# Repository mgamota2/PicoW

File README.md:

# picoW
Raspberry Pi Pico W Projects

## Overview
All of these projects are personal projects which I have completed and implemented. Justifications and media can be found on my github.io page. I have found the Pico W to be an extremely versatile platform for the development of all kinds of embedded systems projects. All of these projects use the on-board WiFi chip.

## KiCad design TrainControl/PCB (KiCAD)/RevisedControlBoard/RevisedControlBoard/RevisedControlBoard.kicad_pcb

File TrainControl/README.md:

# DC Train Control
This project offers an LAN solution for DC model train control

## Overview
This project includes both hardware design and firmware for the Raspberry Pi Pico written in Micropython. The hardware is designed as a hub which can control the speed and
direction of the train as well as switch electrically switching tracks. The hub is controlled from a Raspberry Pi Pico hosted web server which has a dashboard for user 
inputs, allowing remote control of the train

## File Descriptions
**Files in the Full Control folder support track switching, speed, and direction while files in the Speed Control folder only support speed control.

index.html : This file contains the HTML, CSS, and JavaScript code to create, style, and add functionality to the slider and buttons.

main.py : This file initilizes a train object and parses requests from the server to evaluate user input and change speedm direction, or switching tracks accordingly

train_func.py : This file defines the trackPins and railPins classes which correspond to the switching tracks and train direction and speed, respectively

wifi_init.py : This file defines a helper function to connect the Pico W to a WiFi network and establish the server

### PCB
Since this project includes hardware design, the KiCAD project files are provided. Files under RevisedControlBoard are the working version

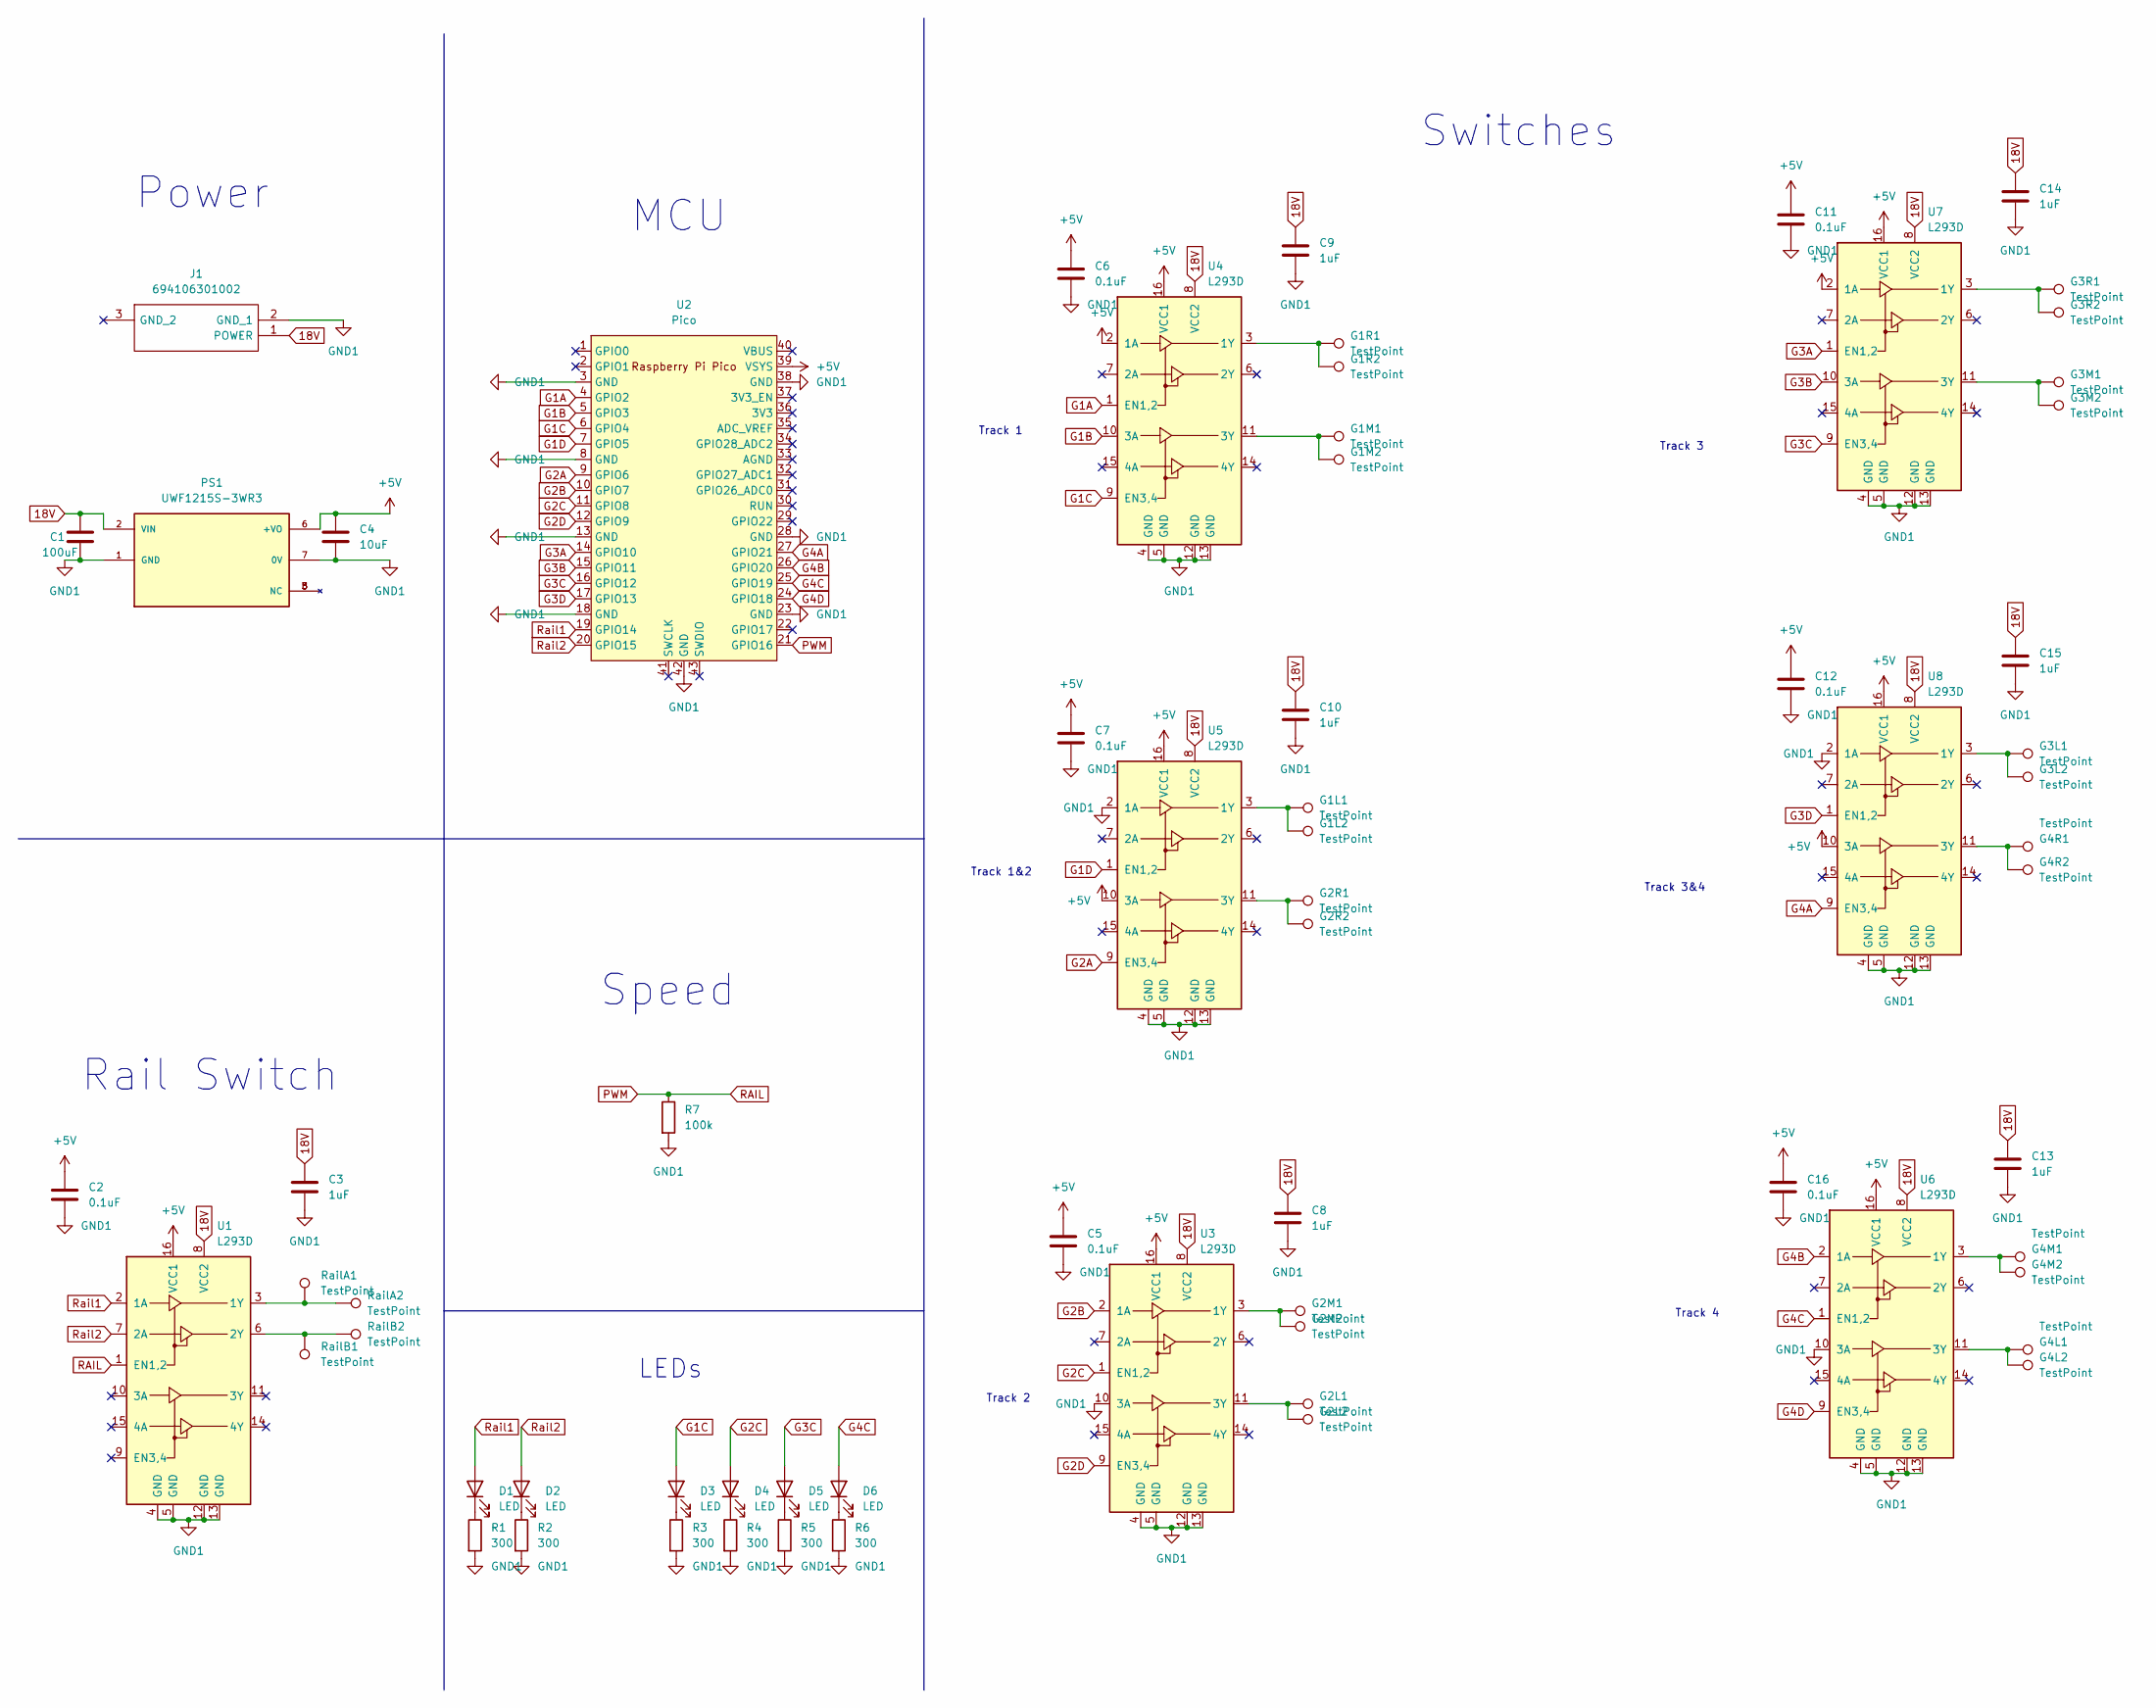
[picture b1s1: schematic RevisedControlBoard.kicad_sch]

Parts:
C1: 100uF; C_1210_3225Metric
C2, C5, C6, C7, C11, C12, C16: 0.1uF; C_1210_3225Metric
C3, C8, C9, C10, C13, C14, C15: 1uF; C_1210_3225Metric
C4: 10uF; C_1210_3225Metric
D1, D2, D3, D4, D5, D6: LED; LED_1812_4532Metric
G1L1, G1L2, G1M1, G1M2, G1R1, G1R2, G2L1, G2L2, G2M1, G2M2, G2R1, G2R2, G3L1, G3L2, G3M1, G3M2, G3R1, G3R2, G4L1, G4L2, G4M1, G4M2, G4R1, G4R2: TestPoint; TestPoint_Pad_2.5x2.5mm
J1: 694106301002; 694106301002_1; Mouser Part Number 710-694106301002
PS1: UWF1215S-3WR3; CONV_UWF1215S-3WR3; PARTREV 2020.08.11-A/1
R1, R2, R3, R4, R5, R6: 300; R_1210_3225Metric
R7: 100k; R_1210_3225Metric
RailA1, RailA2: TestPoint; TestPoint_Pad_2.5x2.5mm
RailB1, RailB2: TestPoint; TestPoint_Pad_2.5x2.5mm
U1, U3, U4, U5, U6, U7, U8: L293D; DIP-16_W7.62mm
U2: Pico; RPi_Pico_SMD_TH

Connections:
18V: C1.1, C3.1, C8.1, C9.1, C10.1, C13.1, C14.1, C15.1, J1.1 (POWER), PS1.2 (VIN), U1.8 (VCC2), U3.8 (VCC2), U4.8 (VCC2), U5.8 (VCC2), U6.8 (VCC2), U7.8 (VCC2), U8.8 (VCC2)
+5V: C2.1, C4.1, C5.1, C6.1, C7.1, C11.1, C12.1, C16.1, PS1.6 (+VO), U1.16 (VCC1), U2.39 (VSYS), U3.16 (VCC1), U4.2 (1A), U4.16 (VCC1), U5.10 (3A), U5.16 (VCC1), U6.16 (VCC1), U7.2 (1A), U7.16 (VCC1), U8.10 (3A), U8.16 (VCC1)
G1A: U2.4 (GPIO2), U4.1 (EN1,2)
G1B: U2.5 (GPIO3), U4.10 (3A)
G1C: D3.2 (A), U2.6 (GPIO4), U4.9 (EN3,4)
G1D: U2.7 (GPIO5), U5.1 (EN1,2)
G2A: U2.9 (GPIO6), U5.9 (EN3,4)
G2B: U2.10 (GPIO7), U3.2 (1A)
G2C: D4.2 (A), U2.11 (GPIO8), U3.1 (EN1,2)
G2D: U2.12 (GPIO9), U3.9 (EN3,4)
G3A: U2.14 (GPIO10), U7.1 (EN1,2)
G3B: U2.15 (GPIO11), U7.10 (3A)
G3C: D5.2 (A), U2.16 (GPIO12), U7.9 (EN3,4)
G3D: U2.17 (GPIO13), U8.1 (EN1,2)
G4A: U2.27 (GPIO21), U8.9 (EN3,4)
G4B: U2.26 (GPIO20), U6.2 (1A)
G4C: D6.2 (A), U2.25 (GPIO19), U6.1 (EN1,2)
G4D: U2.24 (GPIO18), U6.9 (EN3,4)
GND1: C1.2, C2.2, C3.2, C4.2, C5.2, C6.2, C7.2, C8.2, C9.2, C10.2, C11.2, C12.2, C13.2, C14.2, C15.2, C16.2, J1.2 (GND_1), PS1.1 (GND), PS1.7 (0V), R1.2, R2.2, R3.2, R4.2, R5.2, R6.2, R7.2, U1.4 (GND), U1.5 (GND), U1.12 (GND), U1.13 (GND), U2.3 (GND), U2.8 (GND), U2.13 (GND), U2.18 (GND), U2.23 (GND), U2.28 (GND), U2.38 (GND), U2.42 (GND), U3.4 (GND), U3.5 (GND), U3.10 (3A), U3.12 (GND), U3.13 (GND), U4.4 (GND), U4.5 (GND), U4.12 (GND), U4.13 (GND), U5.2 (1A), U5.4 (GND), U5.5 (GND), U5.12 (GND), U5.13 (GND), U6.4 (GND), U6.5 (GND), U6.10 (3A), U6.12 (GND), U6.13 (GND), U7.4 (GND), U7.5 (GND), U7.12 (GND), U7.13 (GND), U8.2 (1A), U8.4 (GND), U8.5 (GND), U8.12 (GND), U8.13 (GND)
unnamed: D1.1 (K), R1.1
unnamed: D2.1 (K), R2.1
unnamed: D3.1 (K), R3.1
unnamed: D4.1 (K), R4.1
unnamed: D5.1 (K), R5.1
unnamed: D6.1 (K), R6.1
unnamed: G1L1.1, G1L2.1, U5.3 (1Y)
unnamed: G1M1.1, G1M2.1, U4.11 (3Y)
unnamed: G1R1.1, G1R2.1, U4.3 (1Y)
unnamed: G2L1.1, G2L2.1, U3.11 (3Y)
unnamed: G2M1.1, G2M2.1, U3.3 (1Y)
unnamed: G2R1.1, G2R2.1, U5.11 (3Y)
unnamed: G3L1.1, G3L2.1, U8.3 (1Y)
unnamed: G3M1.1, G3M2.1, U7.11 (3Y)
unnamed: G3R1.1, G3R2.1, U7.3 (1Y)
unnamed: G4L1.1, G4L2.1, U6.11 (3Y)
unnamed: G4M1.1, G4M2.1, U6.3 (1Y)
unnamed: G4R1.1, G4R2.1, U8.11 (3Y)
unnamed: RailA1.1, RailA2.1, U1.3 (1Y)
unnamed: RailB1.1, RailB2.1, U1.6 (2Y)
PWM: R7.1, U1.1 (EN1,2), U2.21 (GPIO16)
Rail1: D1.2 (A), U1.2 (1A), U2.19 (GPIO14)
Rail2: D2.2 (A), U1.7 (2A), U2.20 (GPIO15)

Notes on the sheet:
MCU
Power
LEDs
Track 1&2
Track 3&4
Track 3
Track 2
Switches
Track 4
Track 1
Speed
Rail Switch

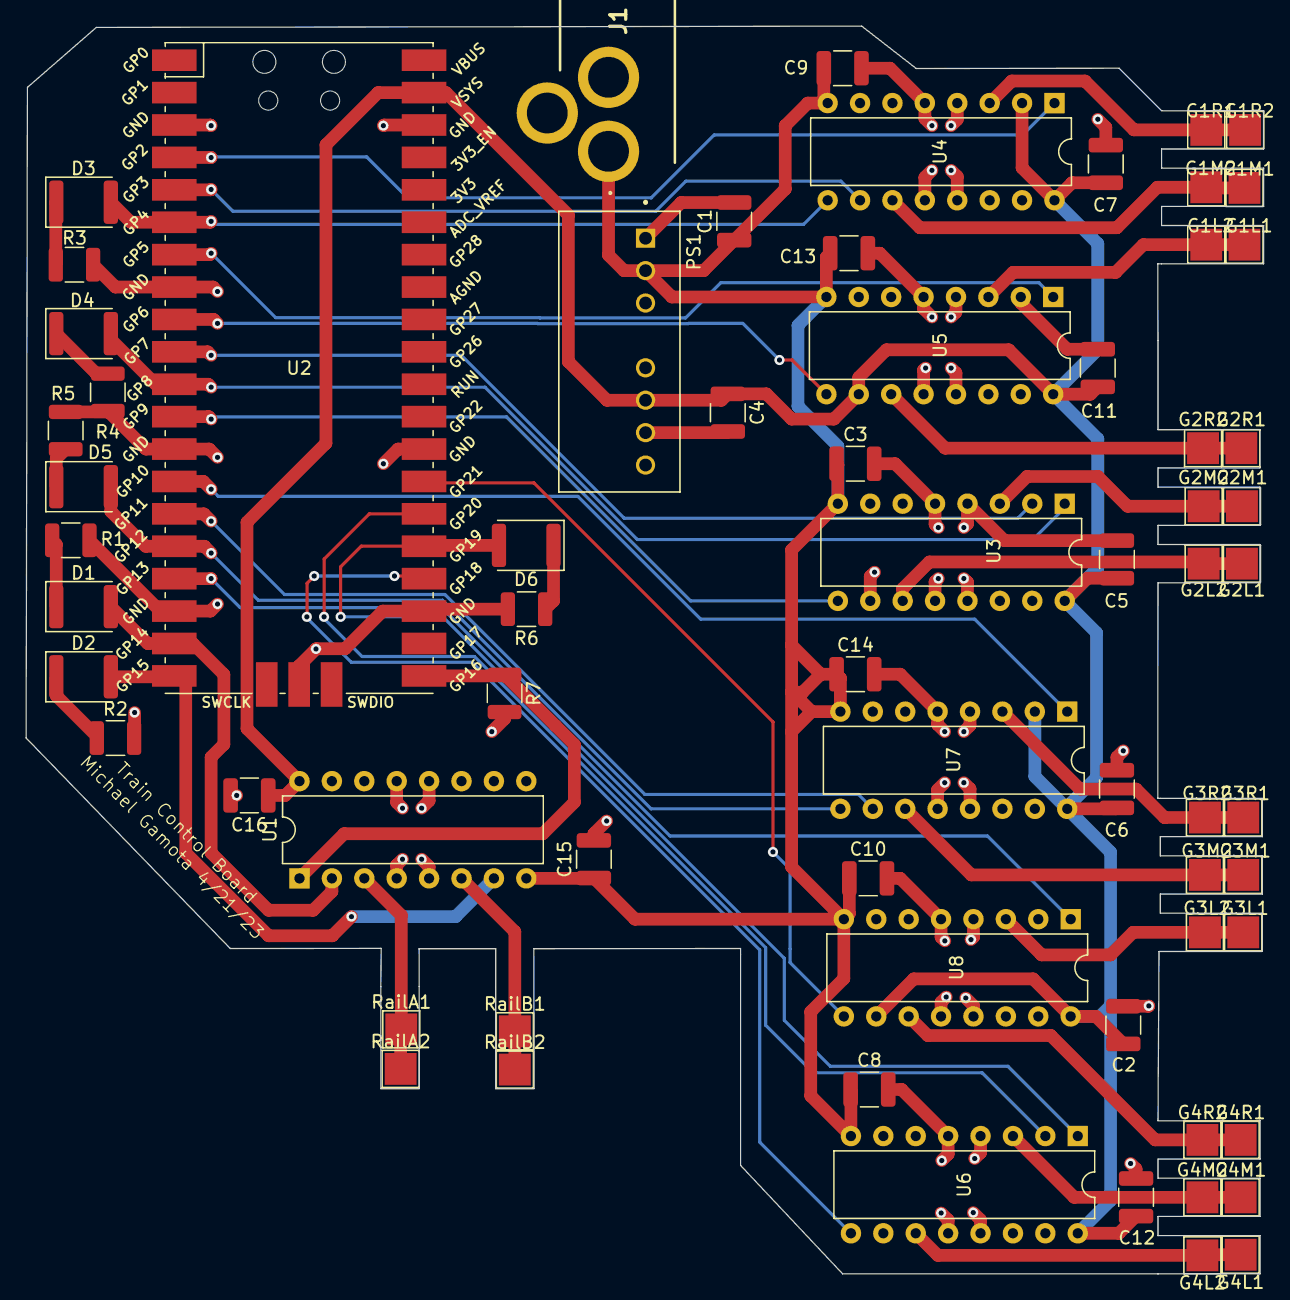
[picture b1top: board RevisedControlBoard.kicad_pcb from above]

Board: 2 copper layers, 97.0 x 97.8 mm, 67 parts (0 on the bottom side), 42 nets.

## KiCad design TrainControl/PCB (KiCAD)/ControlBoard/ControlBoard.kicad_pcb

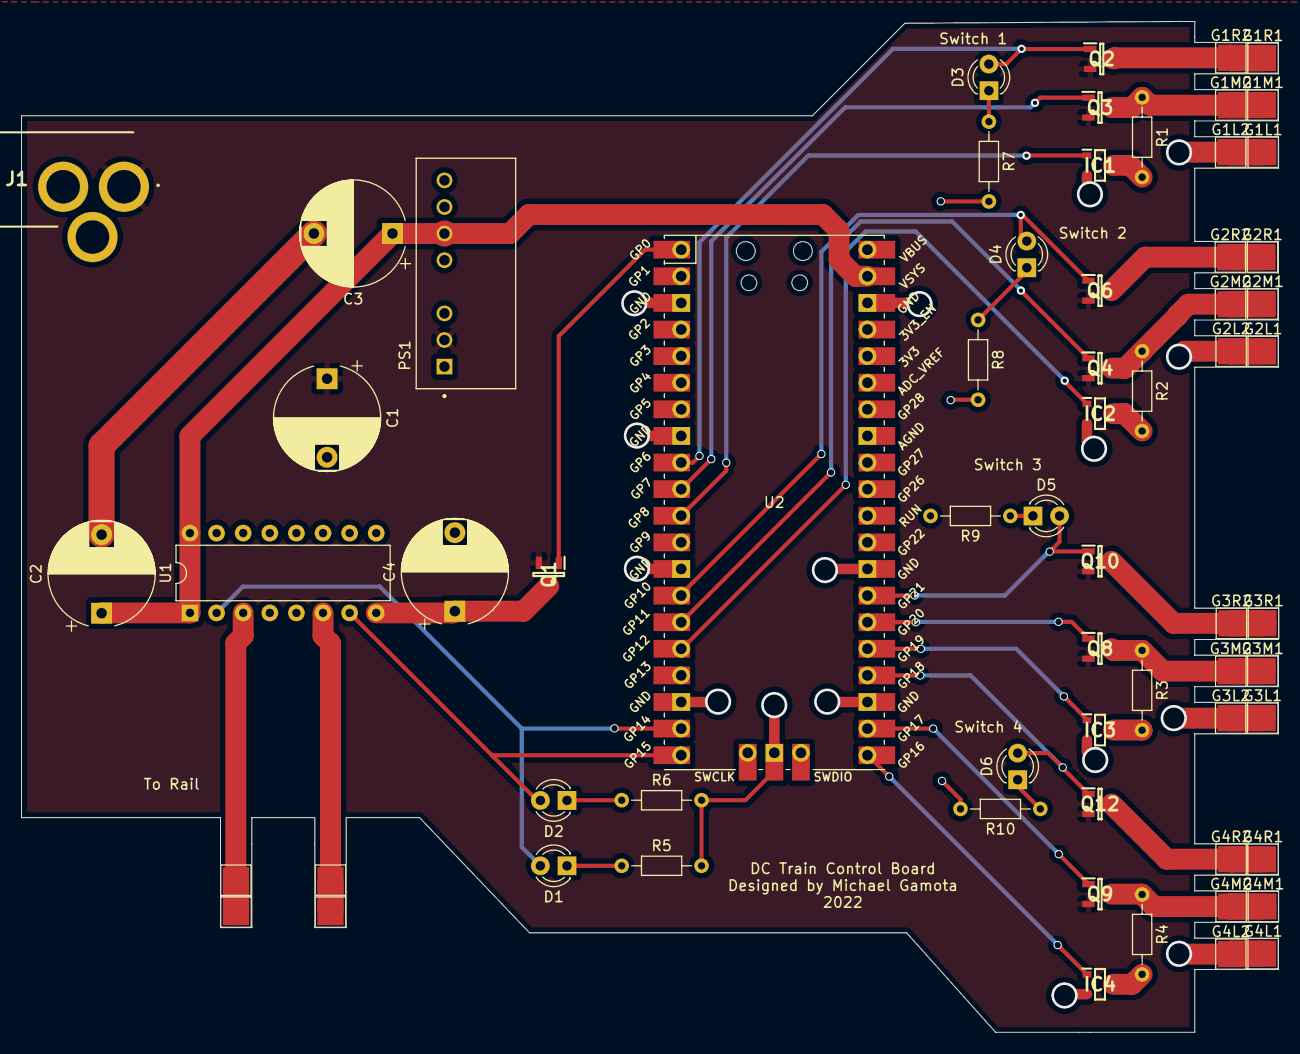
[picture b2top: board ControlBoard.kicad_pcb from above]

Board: 2 copper layers, 120.0 x 96.5 mm, 65 parts (0 on the bottom side), 40 nets.

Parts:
C1: 100uF; CP_Radial_D10.0mm_P7.50mm
C2: 0.1uF; CP_Radial_D10.0mm_P7.50mm
C3: 10uF; CP_Radial_D10.0mm_P7.50mm
C4: 1uF; CP_Radial_D10.0mm_P7.50mm
D1, D2, D3, D4, D5, D6: LED; LED_D3.0mm
G1L1, G1L2, G1M1, G1M2, G1R1, G1R2, G2L1, G2L2, G2M1, G2M2, G2R1, G2R2, G3L1, G3L2, G3M1, G3M2, G3R1, G3R2, G4L1, G4L2, G4M1, G4M2, G4R1, G4R2: TestPoint; TestPoint_Pad_2.5x2.5mm
IC1, IC2, IC3, IC4: PJA3404_R1_00001; SOT95P240X110-3N
J1: 694106301002; 694106301002_1
PS1: UWF1215S-3WR3; CONV_UWF1215S-3WR3
Q1, Q2, Q3, Q4, Q6, Q8, Q9, Q10, Q12: NDS332P; SOT95P237X112-3N
R1, R2, R3, R4: 10k; R_Axial_DIN0204_L3.6mm_D1.6mm_P7.62mm_Horizontal
R5, R6, R7, R8, R9, R10: 300; R_Axial_DIN0204_L3.6mm_D1.6mm_P7.62mm_Horizontal
RailA1, RailA2: TestPoint; TestPoint_Pad_2.5x2.5mm
RailB1, RailB2: TestPoint; TestPoint_Pad_2.5x2.5mm
U1: L293D; DIP-16_W7.62mm
U2: Pico; RPi_Pico_SMD_TH

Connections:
18V: C1.1, J1.1 (POWER), PS1.2 (VIN), Q1.2, Q2.2, Q3.2, Q4.2, Q6.2, Q8.2, Q9.2, Q10.2, Q12.2
+5V: C2.1, C3.1, PS1.6 (+VO), U1.1 (EN1,2), U1.16 (VCC1), U2.39 (VSYS)
G1A: D3.2 (A), Q2.1, U2.9 (GPIO6)
G1B: Q3.1, U2.10 (GPIO7)
G1C: IC1.1 (G), U2.11 (GPIO8)
G2A: D4.2 (A), Q6.1, U2.14 (GPIO10)
G2B: Q4.1, U2.15 (GPIO11)
G2C: IC2.1 (G), U2.16 (GPIO12)
G3A: D5.2 (A), Q10.1, U2.27 (GPIO21)
G3B: Q8.1, U2.26 (GPIO20)
G3C: IC3.1 (G), U2.25 (GPIO19)
G4A: D6.2 (A), Q12.1, U2.24 (GPIO18)
G4B: Q9.1, U2.22 (GPIO17)
G4C: IC4.1 (G), U2.21 (GPIO16)
GND: C2.2, C3.2, PS1.7 (0V), R5.2, R6.2, R7.2, R8.2, R9.2, R10.2, U2.3 (GND), U2.8 (GND), U2.13 (GND), U2.18 (GND), U2.23 (GND), U2.28 (GND), U2.38 (GND), U2.42 (GND)
GND1: C1.2, C4.2, G1L1.1, G1L2.1, G2L1.1, G2L2.1, G3L1.1, G3L2.1, G4L1.1, G4L2.1, IC1.2 (S), IC2.2 (S), IC3.2 (S), IC4.2 (S), J1.2 (GND_1), J1.3 (GND_2), PS1.1 (GND), U1.4 (GND), U1.5 (GND), U1.12 (GND), U1.13 (GND)
unnamed: D1.1 (K), R5.1
unnamed: D2.1 (K), R6.1
unnamed: D3.1 (K), R7.1
unnamed: D4.1 (K), R8.1
unnamed: D5.1 (K), R9.1
unnamed: D6.1 (K), R10.1
unnamed: G1M1.1, G1M2.1, Q3.3, R1.1
unnamed: G1R1.1, G1R2.1, Q2.3
unnamed: G2M1.1, G2M2.1, Q4.3, R2.1
unnamed: G2R1.1, G2R2.1, Q6.3
unnamed: G3M1.1, G3M2.1, Q8.3, R3.1
unnamed: G3R1.1, G3R2.1, Q10.3
unnamed: G4M1.1, G4M2.1, Q9.3, R4.1
unnamed: G4R1.1, G4R2.1, Q12.3
unnamed: IC1.3 (D), R1.2
unnamed: IC2.3 (D), R2.2
unnamed: IC3.3 (D), R3.2
unnamed: IC4.3 (D), R4.2
unnamed: RailA1.1, RailA2.1, U1.3 (1Y)
unnamed: RailB1.1, RailB2.1, U1.6 (2Y)
PWM: Q1.1, U2.1 (GPIO0)
RAIL: C4.1, Q1.3, U1.8 (VCC2)
Rail1: D1.2 (A), U1.2 (1A), U2.19 (GPIO14)
Rail2: D2.2 (A), U1.7 (2A), U2.20 (GPIO15)

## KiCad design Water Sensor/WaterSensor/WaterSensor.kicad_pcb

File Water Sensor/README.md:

# Water Sensor Project

## Overview
This project is a solution for detecting water leaks. The system uses the umail repo for MicroPython (https://github.com/shawwwn/uMail). When a leak is detected on the 
sensor board, a buzzer on the analog section of the board goes off along with an LED. The reading on the ADC pin of the Pico W will trigger an alert to be sent to the specified
email using SMTP. There is also a voltage divider connected to the ADC to read battery level if being powered with a battery, an alert is sent when battery is low.

## Files Overview
The Code directory contains the MicroPython firmware.

main.py : Reads ADC values to determine if there is a leak/low battery

umail.py : 3rd party library used to send email alert

### PCB Files
The WaterSensor directory contains the KiCAD project files for the main board which has the buzzer, Raspberry Pi Pico W, etc.

The WaterSensorTraces directory contains the KiCAD project files for the sensor itself

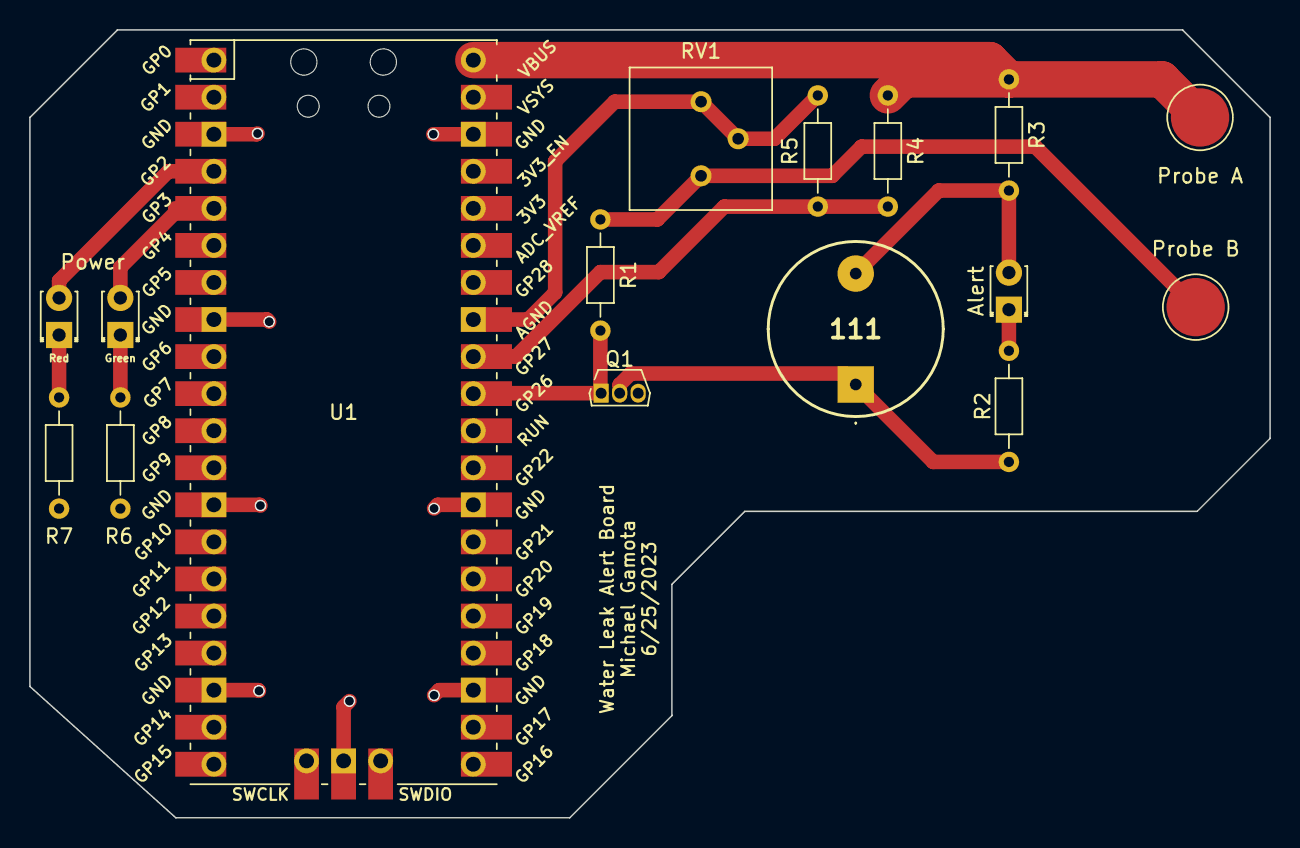
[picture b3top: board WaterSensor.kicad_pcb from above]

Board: 2 copper layers, 85.0 x 54.0 mm, 16 parts (0 on the bottom side), 13 nets.

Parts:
111: CEM-1205-IC; CEM1205IC
Alert: LED; LED_D1.8mm_W3.3mm_H2.4mm
Power, Power2: LED; LED_D1.8mm_W3.3mm_H2.4mm
Probe A: TestPoint; TestPoint_Pad_D4.0mm
Probe B: TestPoint; TestPoint_Pad_D4.0mm
Q1: Q_NPN_BCE; TO-92S
R1: 1k; R_Axial_DIN0204_L3.6mm_D1.6mm_P7.62mm_Horizontal
R2, R6, R7: 220; R_Axial_DIN0204_L3.6mm_D1.6mm_P7.62mm_Horizontal
R3: 47; R_Axial_DIN0204_L3.6mm_D1.6mm_P7.62mm_Horizontal
R4: 30k; R_Axial_DIN0204_L3.6mm_D1.6mm_P7.62mm_Horizontal
R5: 10k; R_Axial_DIN0204_L3.6mm_D1.6mm_P7.62mm_Horizontal
RV1: 47k; Potentiometer_Bourns_3386P_Vertical
U1: Pico; RPi_Pico_SMD_TH

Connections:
+5V: Probe A.1, R3.1, R4.1, U1.40 (VBUS)
AGND: R5.2, RV1.2, RV1.3, U1.33 (AGND)
AnalogOut: Q1.1 (B), R1.2, U1.31 (GPIO26_ADC0)
BatGood: Power.2 (A), U1.5 (GPIO3)
BatLow: Power2.2 (A), U1.4 (GPIO2)
BatteryLevel: R4.2, R5.1, U1.32 (GPIO27_ADC1)
GND: Q1.3 (E), R6.2, R7.2, U1.3 (GND), U1.8 (GND), U1.13 (GND), U1.18 (GND), U1.23 (GND), U1.28 (GND), U1.38 (GND), U1.42 (GND)
unnamed: Alert.1 (K), R2.1
unnamed: 111.2, Alert.2 (A), R3.2
unnamed: Power.1 (K), R6.1
unnamed: Power2.1 (K), R7.1
unnamed: 111.1, Q1.2 (C), R2.2
unnamed: Probe B.1, R1.1, RV1.1

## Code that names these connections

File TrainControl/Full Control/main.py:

import machine
import socket
import network
import time
import ubinascii
from wifi_pw import secrets
from wifi_init import *
from train_func import *



led=machine.Pin('LED', machine.Pin.OUT)

#Create objects for track switches, rail control, and speed control
track1 = trackPins(2, 3, 4, 5)
track2 = trackPins(6, 7, 8, 9)
track3 = trackPins(10,11,12,13)
track4 = trackPins(21, 20, 19, 18)

track1.setState(0)
track2.setState(0)
track3.setState(0)
track4.setState(0)


railObj = railPins(14, 15)
railObj.setState(1)


speed = machine.PWM(machine.Pin(16))
duty_u16=(0)
speed.freq(5000)

# Track 1
# State 1: G1A = 1 | G1B = 0 | G1C = 1 | G1D = 0
# State 2: G1A = 0 | G1B = 1 | G1C = 1 | G1D = 1

#Track 2
# State 1: G2A = 1 | G2B = 0 | G2C = 1 | G2D = 0
# State 2: G2A = 0 | G2B = 1 | G2C = 1 | G2D = 1

x = init_wifi()
led.value(x)
# HTTP server with socket
addr = socket.getaddrinfo('0.0.0.0', 80)[0][-1]

s = socket.socket()
s.setsockopt(socket.SOL_SOCKET, socket.SO_REUSEADDR, 1)
s.bind(addr)
s.listen(1)

print('Listening on', addr)

# Listen for connections
while True:
    try:
        
        conn, addr = s.accept()
        
        print('Got a connection from %s' % str(addr))
        request = conn.recv(1024)
        if "signed-exchange" in str(request):
            pass
        print('Content = %s' % str(request))
        request = str(request)
        
        
        if (request.find('button2')!=-1):
            print('Stopping')
            stop(speed)
            

        else:
            index1 = request.find('slider=')  + len('slider=')
            
            #Parse int
            try:
                if request[index1].isdigit():
                    offset = 1
                    if request[index1+1].isdigit():
                        offset = 2
                        if request[index1+2].isdigit():
                            offset = 3
                    duty = (int(request[index1:index1+offset])*230)+26200
                    print(duty, '\n')
                    speed.duty_u16(duty)
            except:
                pass
                
          
            if (request.find('button3')!=-1) and railObj.getState()==0:
                print('switching direction')
                stop(speed)
                print('Forwards')
                railObj.setState(1)
            
            if (request.find('button1')!=-1) and railObj.getState()==1:
                print('switching direction')
                stop(speed)
                print('Backwards')
                railObj.setState(0)
            
            index2 = request.find('checkbox1=')  + len('checkbox1=')
            if request[index2]=="t" and track1.getState()==False:
                print('Switching track 1')
                track1.setState(1)
            elif request[index2]=="f" and track1.getState()==True:
                print('Switching track 1')
                track1.setState(0)
                
            index3 = request.find('checkbox2=')  + len('checkbox2=')
            if request[index3]=="t" and track2.getState()==False:
                print('Switching track 2')
                track2.setState(1)
            elif request[index3]=="f" and track2.getState()==True:
                print('Switching track 2')
                track2.setState(0)
                
            index4 = request.find('checkbox3=')  + len('checkbox3=')
            if request[index4]=="t" and track3.getState()==False:
                print('Switching track 3')
                track3.setState(1)
            elif request[index4]=="f" and track3.getState()==True:
                print('Switching track 3')
                track3.setState(0)
                
            index5 = request.find('checkbox4=')  + len('checkbox4=')
            if request[index5]=="t" and track4.getState()==False:
                print('Switching track 1')
                track4.setState(1)
            elif request[index5]=="f" and track4.getState()==True:
                print('Switching track 1')
                track4.setState(0)
            
        
        response = get_html('index.html')
        response = response.replace('slider_value1', str(myround(int((speed.duty_u16()-26200)/230))))
            

        
        conn.send('HTTP/1.0 200 OK\r\nContent-type: text/html\r\n\r\n')
        conn.send(response)
        conn.close()
        led.value(1)
    except OSError as e:
        conn.close()
        s.close()
        led.value(0)
        print('Connection closed')
        break
    except (KeyboardInterrupt):
        conn.close()
        s.close()
        led.value(0)
        print('Connection closed')
        break

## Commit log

2022-11-25 First 3 projects
2023-06-13 New Folder
2023-07-09 Adding projects
2023-07-10 Ticker Tape completed
2023-08-10 Updaing
2023-08-10 Adding PCB
2023-08-10 Updating
